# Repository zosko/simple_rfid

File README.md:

# simple-rfid
Arduino 125Khz RFID emulator / cloner / reader 

Components:
- RFID Reader RMD6300
- Arduino Nano

## Sponsorship

This project is kindly sponsored by [PCBWay](https://pcbway.com).
PCBWay specializes in manufacturing high-quality PCBs and makes them affordable to hobbyist and professionals alike.

The range of services they offer include PCB prototyping, assembly, instant quotes for your order, a verification process by a team
of experts and an easy to use, hassle-free order process.

I'm grateful to PCBWay for the support in creating this project.

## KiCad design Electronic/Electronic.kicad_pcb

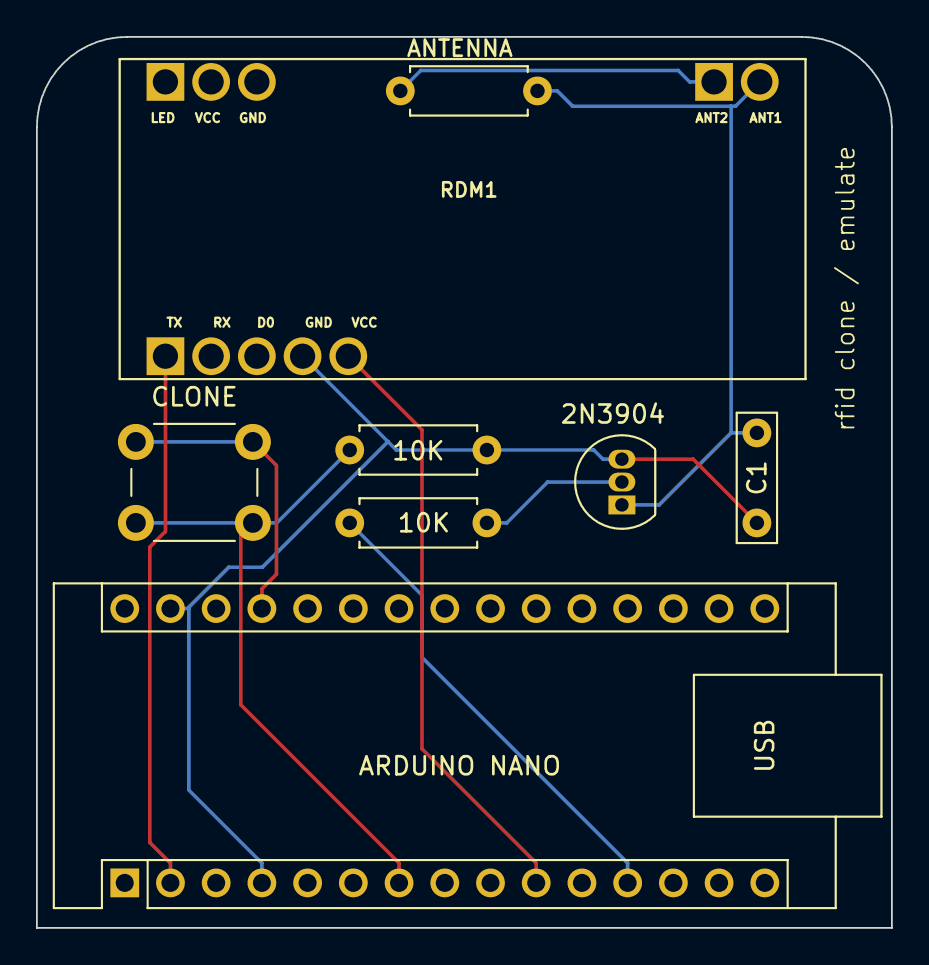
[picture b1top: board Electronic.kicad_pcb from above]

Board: 2 copper layers, 47.5 x 49.5 mm, 8 parts (0 on the bottom side), 9 nets.

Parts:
2N3904: 2N3904; TO-92_Inline
10K, 10K#2: 10K; R_Axial_DIN0207_L6.3mm_D2.5mm_P7.62mm_Horizontal
ANTENNA: L; R_Axial_DIN0207_L6.3mm_D2.5mm_P7.62mm_Horizontal
ARDUINO NANO: Arduino_Nano_v3.x; Arduino_Nano
C1: 10nF; C_Rect_L7.0mm_W2.0mm_P5.00mm
CLONE: SW_Push; SW_PUSH_6mm
RDM1: RDM6300

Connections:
ANT_1: 2N3904.1 (E), ANTENNA.2, C1.2, RDM1.ANT1
ANT_2: ANTENNA.1, RDM1.ANT2
ANT_EMU: 10K#2.1, ARDUINO NANO.12 (D9)
BTN_CLONE: 10K.1, ARDUINO NANO.7 (D4), CLONE.2
GND: 2N3904.3 (C), 10K.2, ARDUINO NANO.4 (GND), ARDUINO NANO.29 (GND), C1.1, RDM1.GND
unnamed: 2N3904.2 (B), 10K#2.2
RFID_POWER: ARDUINO NANO.10 (D7), RDM1.VCC
TX_RFID: ARDUINO NANO.2 (D0/RX), RDM1.TX
VCC: ARDUINO NANO.27 (+5V), CLONE.1

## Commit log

2021-05-13 improvements
    emulator now can store up to 5 cards
2024-12-19 update project
